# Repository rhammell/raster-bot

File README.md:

# Raster Bot

Raster Bot is a compact, two-wheeled differential-drive robot built around an
ESP32 and a capacitive touchscreen display. The project is fully open: it
includes the custom PCB, the 3D-printable mechanical design, the firmware
(packaged as an Arduino library), and the source graphics.

The firmware provides closed-loop motor control with quadrature encoders and
PID speed regulation, battery/charge monitoring, and a touchscreen UI — all
wrapped in a simple high-level API so sketches can drive the bot in a few lines.

## Build guide

A full step-by-step build tutorial — bill of materials, wiring, assembly, and
flashing — is published on Hackster.io:

**[Raster Bot build guide on Hackster.io](https://www.hackster.io/)** <!-- TODO: replace with the real tutorial URL -->

This README focuses on the contents of the repository and the firmware API;
see the Hackster guide if you want to build one from scratch.

## Repository structure

| Folder | Description |
| --- | --- |
| [`firmware/`](firmware/) | ESP32 firmware, packaged as the `Raster_Bot` Arduino library, plus example and tuning sketches. |
| [`hardware/`](hardware/) | KiCad project for the custom PCB (schematic, board layout, and footprint/symbol libraries). |
| [`mechanical/`](mechanical/) | FreeCAD model of the chassis and mechanical parts. |
| [`graphics/`](graphics/) | Logo artwork — SVG source and exported PNGs used for the board silkscreen and the boot splash screen. |

### `firmware/`

The firmware lives in `firmware/Raster_Bot/`, structured as an Arduino library:

| Path | Description |
| --- | --- |
| `src/Raster_Bot.h` / `.cpp` | Top-level `Raster_Bot` class that ties the subsystems together. |
| `src/definitions/` | Compile-time configuration: `pin_definitions.h` (wiring) and `robot_definitions.h` (tuning/behavior). |
| `src/display/` | `Raster_Display` — TFT, capacitive touch, and backlight control (plus the splash logo). |
| `src/battery/` | `Raster_Battery` — battery voltage and charger-status monitoring. |
| `src/drive/` | Differential drive stack: `Raster_Motor`, `Raster_Encoder`, `Raster_PID`, `Raster_Motor_Controller`, and `Raster_Drive`. |
| `examples/` | Standalone feature demos: `BatteryTest`, `GraphicsTest`, `TouchTest`. |
| `tuning/` | Calibration sketches, numbered in the order they should be run: `1_FeedforwardTuning`, `2_PIDTuning`, `3_WheelSyncTuning`, `4_DistanceTuning`. |
| `tests/` | Post-build verification sketches: `ForwardTest`, `DriftTest`. |
| `library.properties` | Arduino library metadata and dependencies. |

**Dependencies** (install via the Arduino Library Manager): Adafruit GFX
Library, Adafruit ILI9341, Adafruit FT6206 Library. Target architecture is
`esp32`.

### `hardware/`

KiCad design for the Raster Bot PCB. Open `hardware/Raster_Bot/Raster_Bot.kicad_pro`
in KiCad to view the schematic and board. Project-local footprint, symbol, and
3D-model libraries are under `hardware/Raster_Bot/libraries/`.

### `mechanical/`

FreeCAD source (`mechanical/src/Raster_Bot.FCStd`) for the robot's mechanical
design, parameterized for resizing.

### `graphics/`

- `src/raster_logo.svg` — master logo artwork.
- `export/raster_logo_silkscreen.png` — logo for the PCB silkscreen.
- `export/raster_logo_splash.png` — logo shown on the display at boot.

## Firmware API

Include the library and create a single `Raster_Bot` instance. It exposes three
subsystems as public members: `display`, `battery`, and `drive`.

```cpp
#include <Raster_Bot.h>

Raster_Bot bot;

void setup() {
    Serial.begin(115200);
    if (!bot.begin()) {
        Serial.println("Raster Bot init failed");
        while (1);
    }
    bot.drive.straight(10.0f);   // drive forward at 10 cm/s
}

void loop() {
    bot.drive.update();          // must be called frequently for PID control
}
```

### `Raster_Bot`

| Method | Description |
| --- | --- |
| `bool begin()` | Initializes the display, battery monitor, and drive subsystems. Returns `false` if any fail. |
| `display` | `Raster_Display` instance (see below). |
| `battery` | `Raster_Battery` instance (see below). |
| `drive` | `Raster_Drive` instance (see below). |

### `Raster_Display`

Extends Adafruit's `Adafruit_ILI9341`, so all standard Adafruit GFX drawing
calls are available in addition to:

| Method | Description |
| --- | --- |
| `bool begin()` | Initializes the TFT, touchscreen, and backlight. |
| `void showSplash()` | Plays the boot splash animation. |
| `void setBrightness(uint8_t brightness)` | Sets backlight brightness (0–255). |
| `bool touched()` | Returns `true` while the screen is being touched. |
| `TS_Point getTouchPoint()` | Returns the current touch point, mapped to the active screen rotation. |

### `Raster_Battery`

| Method | Description |
| --- | --- |
| `void begin()` | Initializes battery/charge-status monitoring. |
| `float voltage()` | Battery voltage in volts. |
| `bool charging()` | `true` while actively charging. |
| `bool chargerConnected()` | `true` when a charging source is plugged in. |

### `Raster_Drive`

Differential drive with per-wheel PID speed control. Call `update()` frequently
from `loop()` to run the control loop.

| Method | Description |
| --- | --- |
| `bool begin()` | Initializes the motor driver, both motor controllers, and encoders. |
| `void straight(float speed_cm_s)` | Drives both wheels at the given speed (negative = reverse). |
| `void stop()` | Stops both motors and goes idle. |
| `void update()` | Runs the drive control loop; call as often as possible. |
| `bool isMoving()` | `true` while a drive command is active. |
| `DriveTelemetry getTelemetry()` | Returns current motor telemetry. |
| `float getDistance()` | Returns cumulative straight-line distance, in cm, driven since power-on. |
| `void resetDistance()` | Resets the cumulative drive distance to zero. |

`DriveTelemetry` contains: `leftRPM`, `leftPWM`, `rightRPM`, `rightPWM`,
`leftCount`, and `rightCount` (wheel-output RPM and raw encoder counts).

## License

<!-- TODO: add a license (e.g. MIT for firmware, CERN-OHL or CC-BY-SA for hardware). -->

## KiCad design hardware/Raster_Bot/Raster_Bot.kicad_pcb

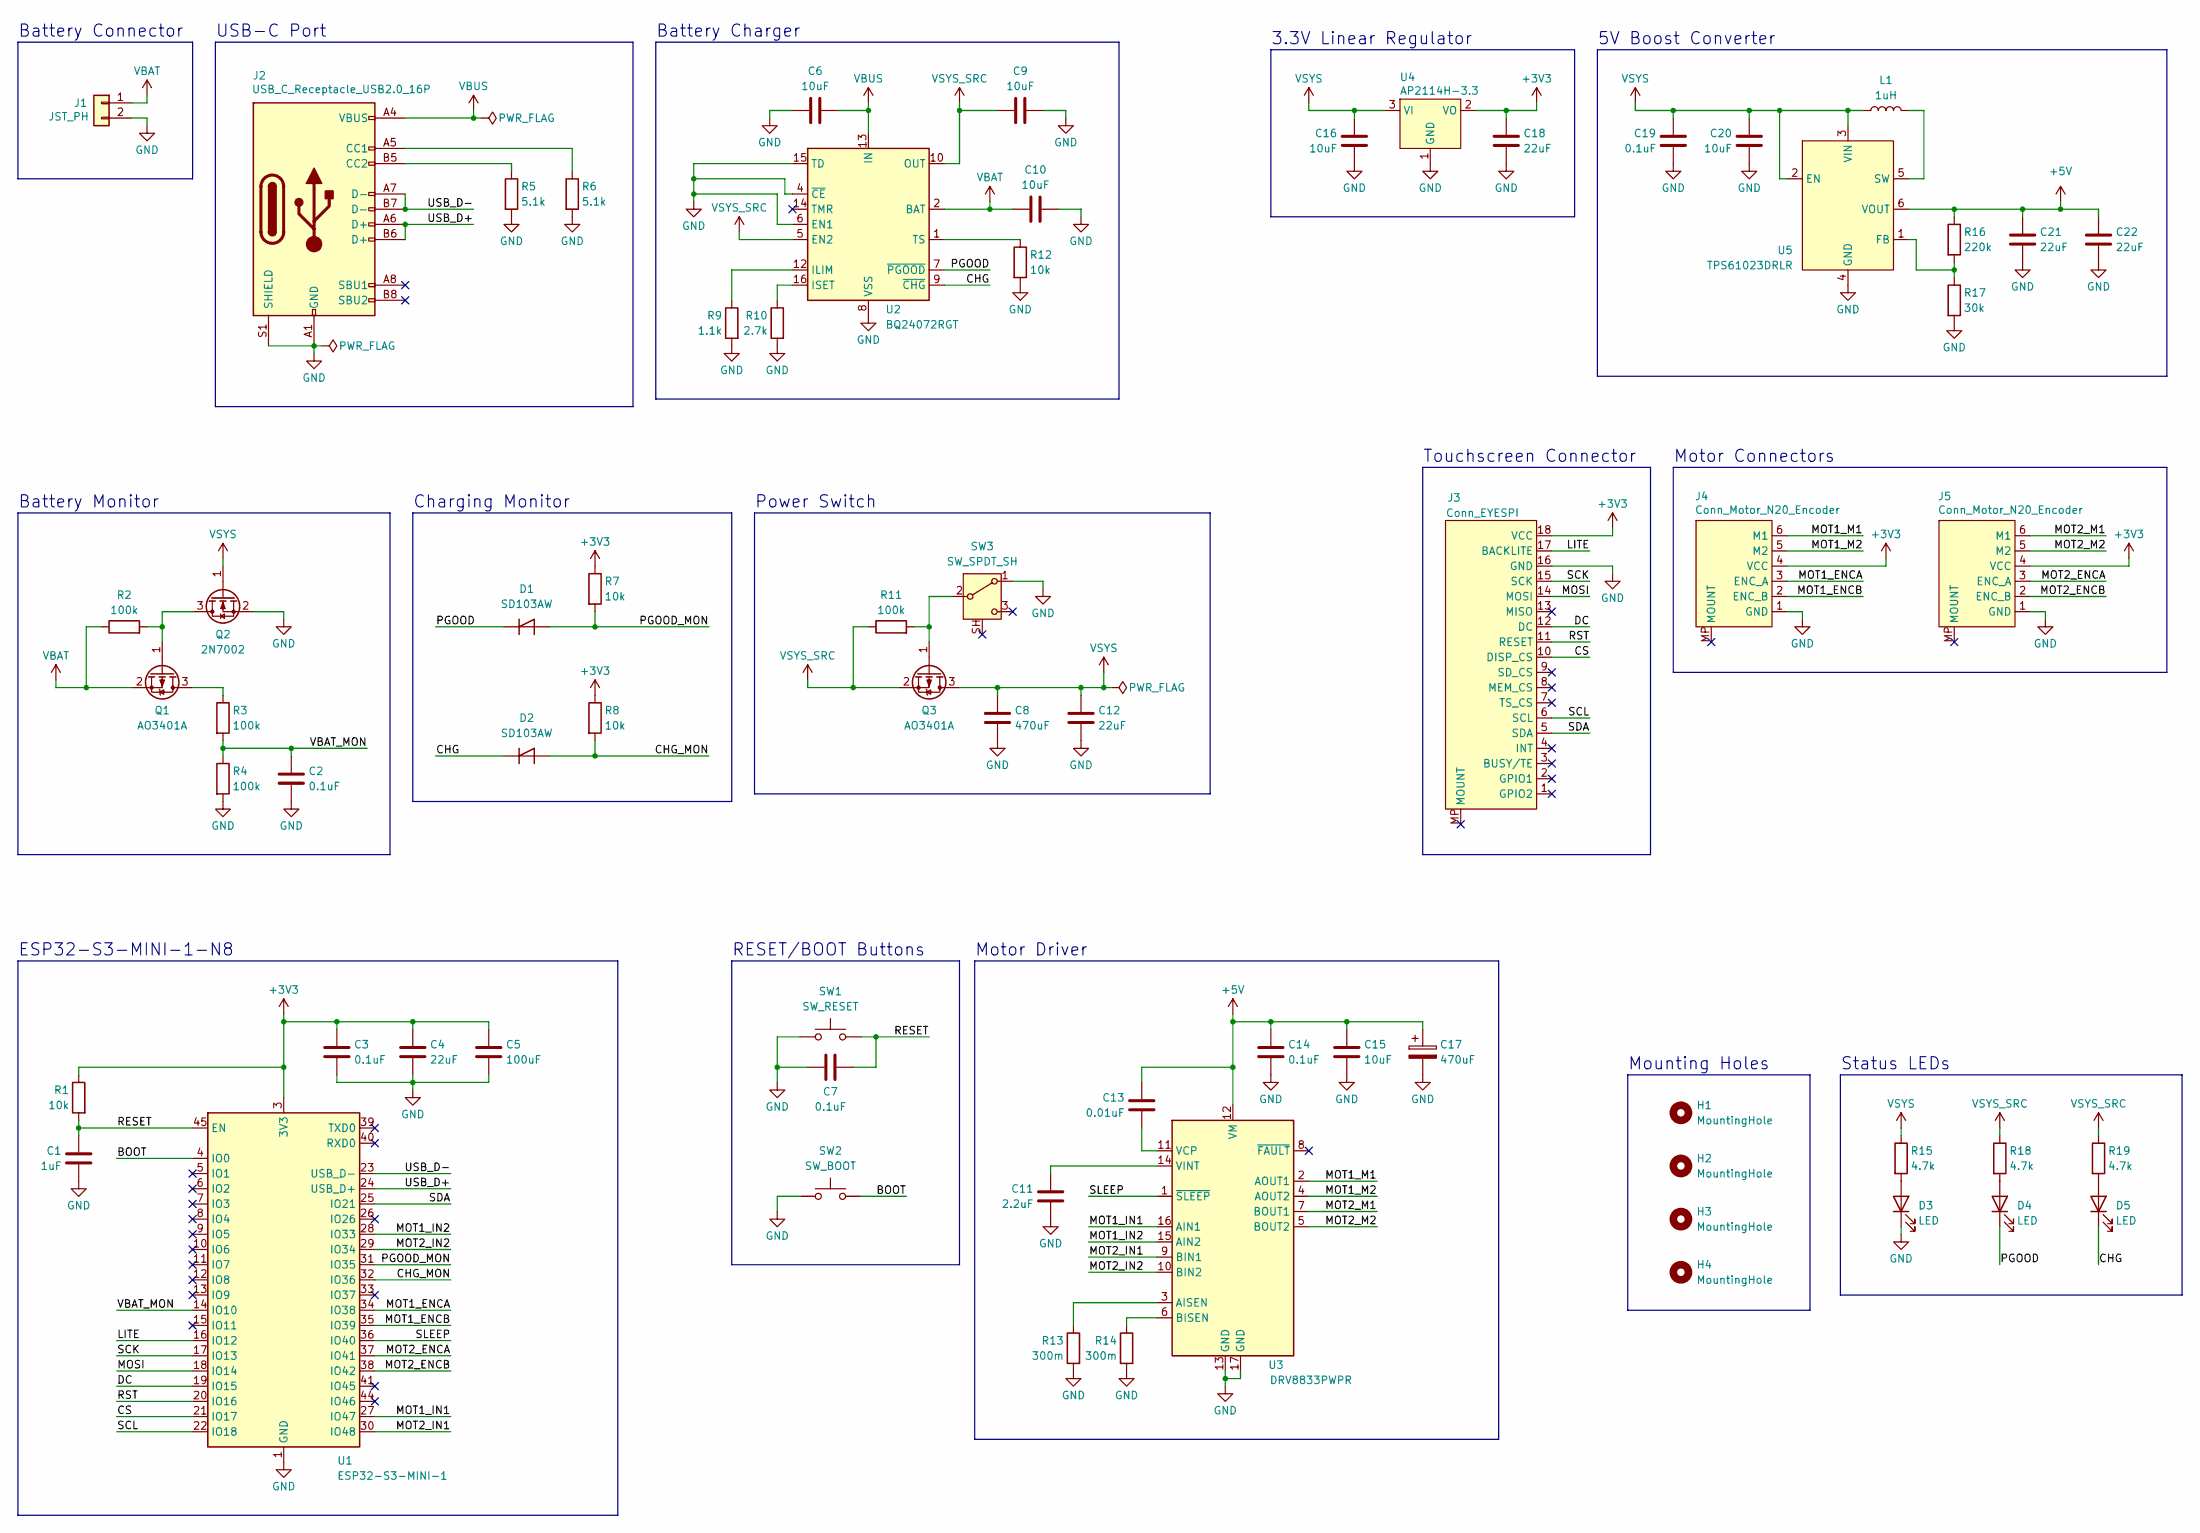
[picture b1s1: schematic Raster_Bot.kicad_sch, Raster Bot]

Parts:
C1: 1uF; C_0603_1608Metric; LCSC C15849
C2, C3, C7, C14, C19: 0.1uF; C_0603_1608Metric; LCSC C14663
C4, C12, C18, C21, C22: 22uF; C_0805_2012Metric; LCSC C45783
C5: 100uF; C_1206_3216Metric; LCSC C15008
C6, C9, C10, C15, C16, C20: 10uF; C_0805_2012Metric; LCSC C15850
C8, C17: 470uF; CP_Elec_6.3x7.7; LCSC C344072
C11: 2.2uF; C_0603_1608Metric; LCSC C23630
C13: 0.01uF; C_0603_1608Metric; LCSC C57112
D1, D2: SD103AW; D_SOD-123; LCSC C7502706
D3: LED; LED_0805_2012Metric; LCSC C2297
D4, D5: LED; LED_0805_2012Metric; LCSC C2296
H1, H2, H3, H4: MountingHole; MountingHole_2.7mm_M2.5
J1: JST_PH; JST_PH_B2B-PH-K_1x02_P2.00mm_Vertical; LCSC C131337
J2: USB_C_Receptacle_USB2.0_16P; USB_C_Receptacle_G-Switch_GT-USB-7010ASV; LCSC C2988369
J3: Conn_EYESPI; XUNPU_FPC-05F-18PH20_1x18-1MP_P0.5mm_Horizontal; LCSC C2856802
J4, J5: Conn_Motor_N20_Encoder; JST_SH_BM06B-SRSS-TB_1x06-1MP_P1.00mm_Vertical; LCSC C495540
L1: 1uH; L_Coilcraft_XxL4030; LCSC C5441341
Q1, Q3: AO3401A; SOT-23; LCSC C15127
Q2: 2N7002; SOT-23; LCSC C8545
R1, R7, R8, R12: 10k; R_0603_1608Metric; LCSC C25804
R2, R3, R4, R11: 100k; R_0603_1608Metric; LCSC C25803
R5, R6: 5.1k; R_0603_1608Metric; LCSC C23186
R9: 1.1k; R_0603_1608Metric; LCSC C22764
R10: 2.7k; R_0603_1608Metric; LCSC C13167
R13, R14: 300m; R_1206_3216Metric; LCSC C22464904
R15, R18, R19: 4.7k; R_0603_1608Metric; LCSC C23162
R16: 220k; R_0603_1608Metric; LCSC C22961
R17: 30k; R_0603_1608Metric; LCSC C22984
SW1: SW_RESET; SW_SPST_TS-1088-xR020; LCSC C720477
SW2: SW_BOOT; SW_SPST_TS-1088-xR020; LCSC C720477
SW3: SW_SPDT_SH; SW_SPDT_Shouhan_MSK12C02; LCSC C431541
U1: ESP32-S3-MINI-1; LCSC C2913206
U2: BQ24072RGT; VQFN-16-1EP_3x3mm_P0.5mm_EP1.6x1.6mm_ThermalVias; LCSC C140288
U3: DRV8833PWPR; HTSSOP-16-1EP_4.4x5mm_P0.65mm_EP3.4x5mm_Mask2.66x2.46mm_The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; LCSC C50506
U4: AP2114H-3.3; SOT-223-3_TabPin2; LCSC C150716
U5: TPS61023DRLR; SOT-563; LCSC C919459

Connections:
+3V3: C3.1, C4.1, C5.1, C18.1, J3.18 (VCC), J4.4 (VCC), J5.4 (VCC), R1.1, R7.1, R8.1, U1.3 (3V3), U4.2 (VO)
+5V: C13.1, C14.1, C15.1, C17.1, C21.1, C22.1, R16.1, U3.12 (VM), U5.6 (VOUT)
/BOOT: SW2.2, U1.4 (IO0)
/CHG: D2.1 (K), D5.1 (K), U2.9 (~CHG)
/CHG_MON: D2.2 (A), R8.2, U1.32 (IO36)
/CS: J3.10 (DISP_CS), U1.21 (IO17)
/DC: J3.12 (DC), U1.19 (IO15)
/LITE: J3.17 (BACKLITE), U1.16 (IO12)
/MOSI: J3.14 (MOSI), U1.18 (IO14)
/MOT1_ENCA: J4.3 (ENC_A), U1.34 (IO38)
/MOT1_ENCB: J4.2 (ENC_B), U1.35 (IO39)
/MOT1_IN1: U1.27 (IO47), U3.16 (AIN1)
/MOT1_IN2: U1.28 (IO33), U3.15 (AIN2)
/MOT1_M1: J4.6 (M1), U3.2 (AOUT1)
/MOT1_M2: J4.5 (M2), U3.4 (AOUT2)
/MOT2_ENCA: J5.3 (ENC_A), U1.37 (IO41)
/MOT2_ENCB: J5.2 (ENC_B), U1.38 (IO42)
/MOT2_IN1: U1.30 (IO48), U3.9 (BIN1)
/MOT2_IN2: U1.29 (IO34), U3.10 (BIN2)
/MOT2_M1: J5.6 (M1), U3.7 (BOUT1)
/MOT2_M2: J5.5 (M2), U3.5 (BOUT2)
/PGOOD: D1.1 (K), D4.1 (K), U2.7 (~PGOOD)
/PGOOD_MON: D1.2 (A), R7.2, U1.31 (IO35)
/RESET: C1.1, C7.1, R1.2, SW1.2, U1.45 (EN)
/RST: J3.11 (RESET), U1.20 (IO16)
/SCK: J3.15 (SCK), U1.17 (IO13)
/SCL: J3.6 (SCL), U1.22 (IO18)
/SDA: J3.5 (SDA), U1.25 (IO21)
/SLEEP: U1.36 (IO40), U3.1 (~SLEEP)
/USB_D+: J2.A6 (D+), J2.B6 (D+), U1.24 (USB_D+)
/USB_D-: J2.A7 (D-), J2.B7 (D-), U1.23 (USB_D-)
/VBAT_MON: C2.1, R3.2, R4.1, U1.14 (IO10)
GND: C1.2, C2.2, C3.2, C4.2, C5.2, C6.1, C7.2, C8.2, C9.2, C10.2, C11.2, C12.2, C14.2, C15.2, C16.2, C17.2, C18.2, C19.2, C20.2, C21.2, C22.2, D3.1 (K), J1.2, J2.A1 (GND), J2.A12 (GND), J2.B1 (GND), J2.B12 (GND), J2.S1 (SHIELD), J3.16 (GND), J4.1 (GND), J5.1 (GND), Q2.2 (S), R4.2, R5.2, R6.2, R9.2, R10.2, R12.2, R13.2, R14.2, R17.2, SW1.1, SW2.1, SW3.1 (A), U1.1 (GND), U1.2 (GND), U1.42 (GND), U1.43 (GND), U1.46 (GND), U1.47 (GND), U1.48 (GND), U1.49 (GND), U1.50 (GND), U1.51 (GND), U1.52 (GND), U1.53 (GND), U1.54 (GND), U1.55 (GND), U1.56 (GND), U1.57 (GND), U1.58 (GND), U1.59 (GND), U1.60 (GND), U1.61 (GND), U1.62 (GND), U1.63 (GND), U1.64 (GND), U1.65 (GND), U2.4 (~CE), U2.6 (EN1), U2.8 (VSS), U2.15 (TD), U2.17 (VSS), U3.13 (GND), U3.17 (GND), U4.1 (GND), U5.4 (GND)
unnamed: D3.2 (A), R15.2
unnamed: D4.2 (A), R18.2
unnamed: D5.2 (A), R19.2
unnamed: J2.A5 (CC1), R6.1
unnamed: J2.B5 (CC2), R5.1
unnamed: Q1.3 (D), R3.1
unnamed: Q1.1 (G), Q2.3 (D), R2.2
unnamed: Q3.1 (G), R11.2, SW3.2 (B)
unnamed: R9.1, U2.12 (ILIM)
unnamed: R10.1, U2.16 (ISET)
unnamed: R12.1, U2.1 (TS)
unnamed: R13.1, U3.3 (AISEN)
unnamed: R14.1, U3.6 (BISEN)
unnamed: C13.2, U3.11 (VCP)
unnamed: C11.1, U3.14 (VINT)
unnamed: R16.2, R17.1, U5.1 (FB)
unnamed: L1.2, U5.5 (SW)
VBAT: C10.1, J1.1, Q1.2 (S), R2.1, U2.2 (BAT), U2.3 (BAT)
VBUS: C6.2, J2.A4 (VBUS), J2.A9 (VBUS), J2.B4 (VBUS), J2.B9 (VBUS), U2.13 (IN)
VSYS: C8.1, C12.1, C16.1, C19.1, C20.1, L1.1, Q2.1 (G), Q3.3 (D), R15.1, U4.3 (VI), U5.2 (EN), U5.3 (VIN)
VSYS_SRC: C9.1, Q3.2 (S), R11.1, R18.1, R19.1, U2.5 (EN2), U2.10 (OUT), U2.11 (OUT)

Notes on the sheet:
Motor Connectors
ESP32-S3-MINI-1-N8
RESET/BOOT Buttons
Battery Charger
Battery Monitor
Touchscreen Connector
Charging Monitor
5V Boost Converter
Status LEDs
3.3V Linear Regulator
Mounting Holes
USB-C Port
Battery Connector
Power Switch
Motor Driver

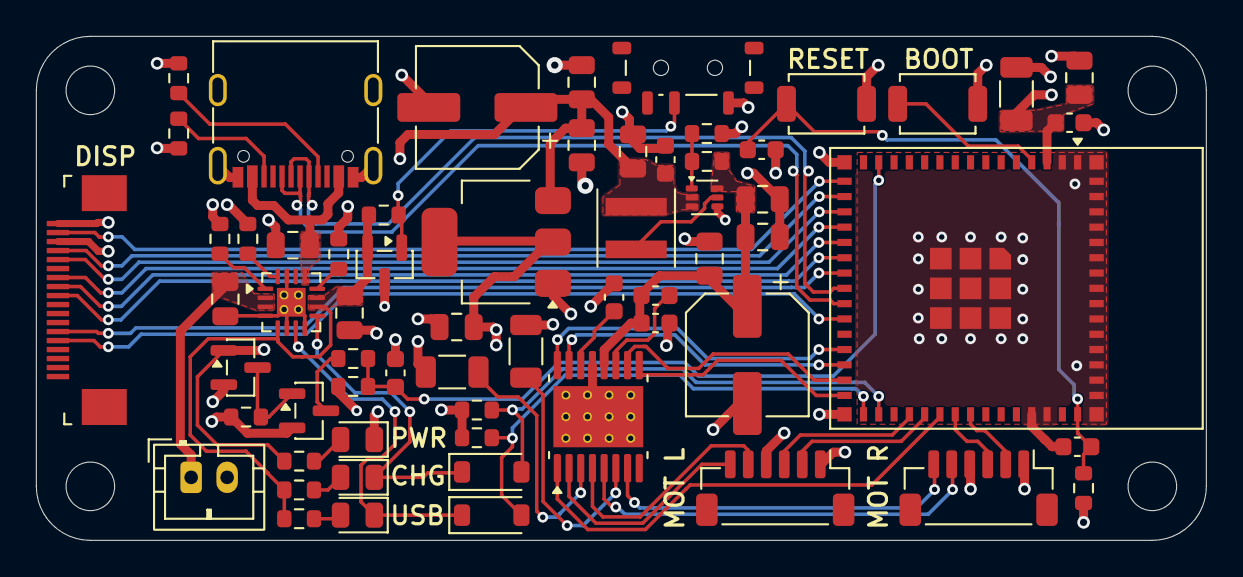
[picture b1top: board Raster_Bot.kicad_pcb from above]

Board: 4 copper layers, 65.0 x 28.0 mm, 67 parts (0 on the bottom side), 54 nets.

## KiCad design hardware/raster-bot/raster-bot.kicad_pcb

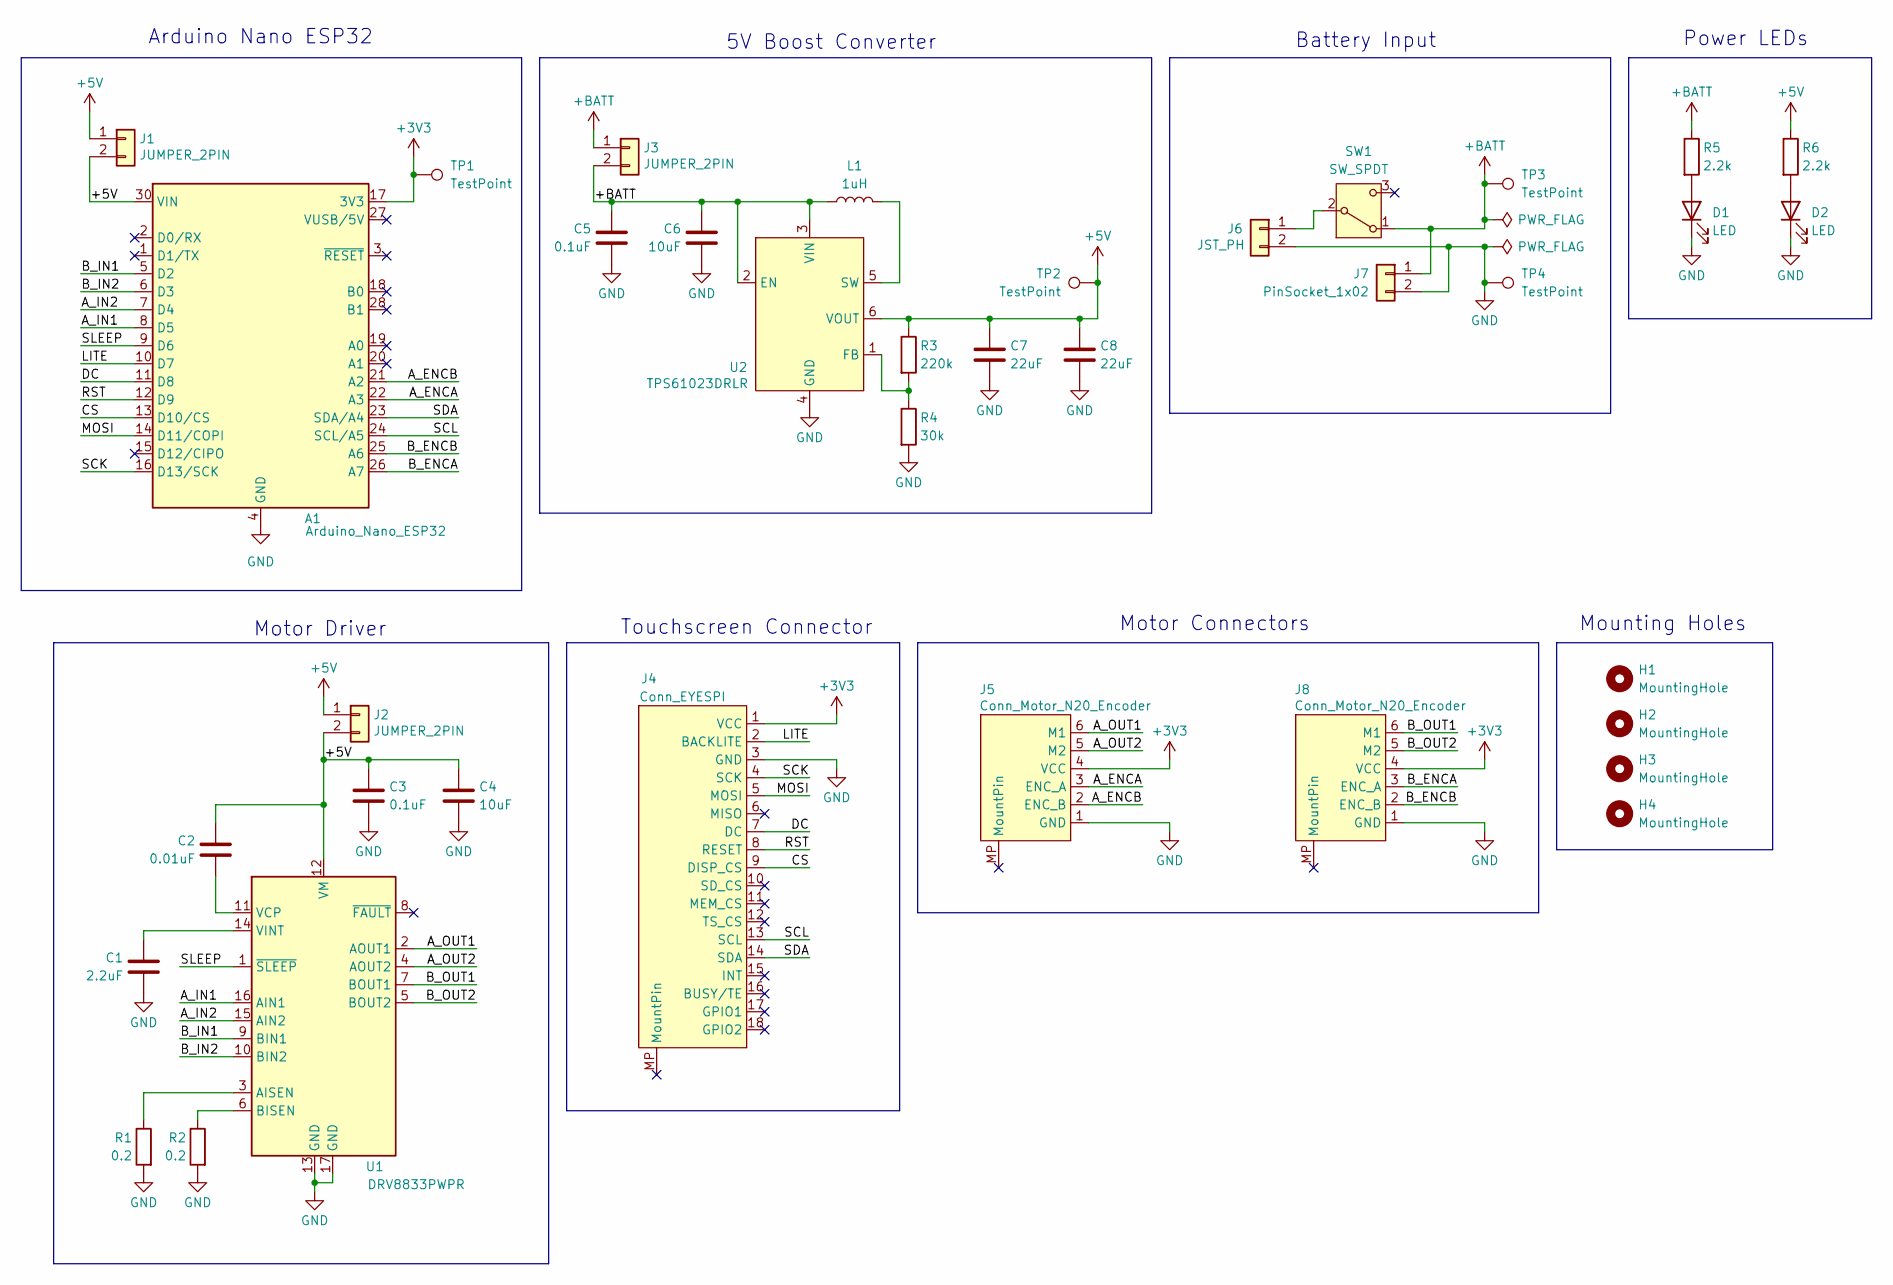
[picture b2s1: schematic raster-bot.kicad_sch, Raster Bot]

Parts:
A1: Arduino_Nano_ESP32; Arduino_Nano
C1: 2.2uF; C_0805_2012Metric; Voltage 6.3; LCSC C377773
C2: 0.01uF; C_0805_2012Metric; Voltage 16; LCSC C1710
C3, C5: 0.1uF; C_0805_2012Metric; LCSC C28233
C4, C6: 10uF; C_0805_2012Metric; LCSC C15850
C7, C8: 22uF; C_0805_2012Metric; LCSC C45783
D1, D2: LED; LED_0603_1608Metric; LCSC C2286
H1, H2, H3, H4: MountingHole; MountingHole_3.2mm_M3
J1, J2, J3: JUMPER_2PIN; PinHeader_1x02_P2.54mm_Vertical; LCSC C124375
J4: Conn_EYESPI; LCSC C2856802
J5, J8: Conn_Motor_N20_Encoder; LCSC C495540
J6: JST_PH; JST_PH_B2B-PH-K_1x02_P2.00mm_Vertical; LCSC C131337
J7: PinSocket_1x02; PinSocket_1x02_P2.54mm_Vertical
L1: 1uH; L_Coilcraft_XxL4030; LCSC C5441341
R1, R2: 0.2; R_1206_3216Metric; LCSC C7467885
R3: 220k; R_0603_1608Metric; LCSC C22961
R4: 30k; R_0603_1608Metric; LCSC C22984
R5, R6: 2.2k; R_0603_1608Metric; LCSC C4190
SW1: SW_SPDT; SW_SPDT_Shouhan_MSK12C02; LCSC C431541
TP1, TP2, TP3, TP4: TestPoint; TestPoint_Pad_1.5x1.5mm
U1: DRV8833PWPR; HTSSOP-16-1EP_4.4x5mm_P0.65mm_EP3.4x5mm_Mask2.66x2.46mm_The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; LCSC C50506
U2: TPS61023DRLR; SOT-563; LCSC C919459

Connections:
+3V3: A1.17 (3V3), J4.1 (VCC), J5.4 (VCC), J8.4 (VCC), TP1.1
+5V: A1.30 (VIN), C2.1, C3.1, C4.1, C7.1, C8.1, J1.1, J1.2, J2.1, J2.2, R3.1, R6.1, TP2.1, U1.12 (VM), U2.6 (VOUT)
+BATT: C5.1, C6.1, J3.1, J3.2, J7.1, L1.1, R5.1, SW1.1 (A), TP3.1, U2.2 (EN), U2.3 (VIN)
/A_ENCA: A1.22 (A3), J5.3 (ENC_A)
/A_ENCB: A1.21 (A2), J5.2 (ENC_B)
/A_IN1: A1.8 (D5), U1.16 (AIN1)
/A_IN2: A1.7 (D4), U1.15 (AIN2)
/A_OUT1: J5.6 (M1), U1.2 (AOUT1)
/A_OUT2: J5.5 (M2), U1.4 (AOUT2)
/B_ENCA: A1.26 (A7), J8.3 (ENC_A)
/B_ENCB: A1.25 (A6), J8.2 (ENC_B)
/B_IN1: A1.5 (D2), U1.9 (BIN1)
/B_IN2: A1.6 (D3), U1.10 (BIN2)
/B_OUT1: J8.6 (M1), U1.7 (BOUT1)
/B_OUT2: J8.5 (M2), U1.5 (BOUT2)
/CS: A1.13 (D10/CS), J4.9 (DISP_CS)
/DC: A1.11 (D8), J4.7 (DC)
/LITE: A1.10 (D7), J4.2 (BACKLITE)
/MOSI: A1.14 (D11/COPI), J4.5 (MOSI)
/RST: A1.12 (D9), J4.8 (RESET)
/SCK: A1.16 (D13/SCK), J4.4 (SCK)
/SCL: A1.24 (SCL/A5), J4.13 (SCL)
/SDA: A1.23 (SDA/A4), J4.14 (SDA)
/SLEEP: A1.9 (D6), U1.1 (~SLEEP)
GND: A1.4 (GND), A1.29 (GND), C1.2, C3.2, C4.2, C5.2, C6.2, C7.2, C8.2, D1.1 (K), D2.1 (K), J4.3 (GND), J5.1 (GND), J6.2, J7.2, J8.1 (GND), R1.2, R2.2, R4.2, TP4.1, U1.13 (GND), U1.17 (GND), U2.4 (GND)
unnamed: D1.2 (A), R5.2
unnamed: D2.2 (A), R6.2
unnamed: J6.1, SW1.2 (B)
unnamed: R1.1, U1.3 (AISEN)
unnamed: R2.1, U1.6 (BISEN)
unnamed: C2.2, U1.11 (VCP)
unnamed: C1.1, U1.14 (VINT)
unnamed: R3.2, R4.1, U2.1 (FB)
unnamed: L1.2, U2.5 (SW)

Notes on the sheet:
Battery Input
Power LEDs
Motor Connectors
Mounting Holes
Touchscreen Connector
Motor Driver
5V Boost Converter
Arduino Nano ESP32

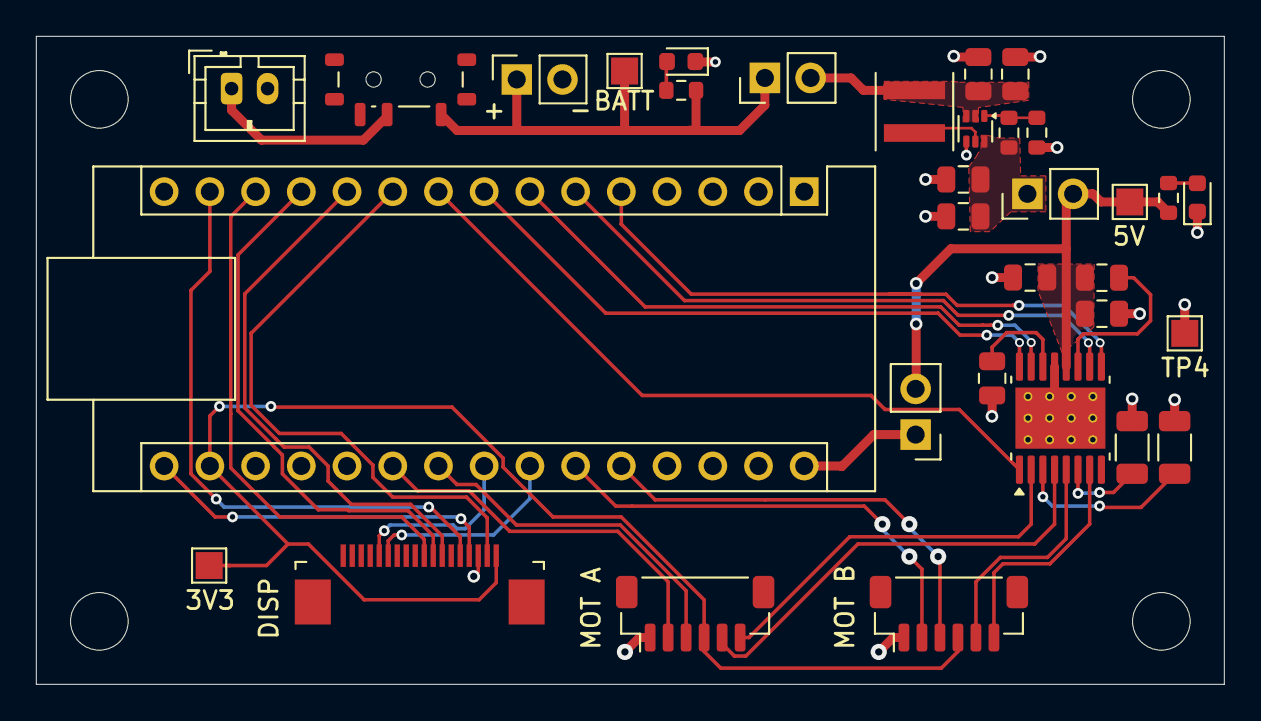
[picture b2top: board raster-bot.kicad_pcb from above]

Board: 2 copper layers, 66.0 x 36.0 mm, 37 parts (0 on the bottom side), 34 nets.

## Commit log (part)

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2026-01-16 Initial commit of v0.1 of hardware PCB design
2026-01-18 PCB v0.2 update - added motor JST connectors; refactored custom footprints
2026-01-28 Refactor filenames to Raster_Bot
2026-02-11 Add initial implementation of Raster_Bot library with configuration, display, and touch functionality; include example sketches for graphics and touch tests.
2026-02-11 Update hardware design for Raster Bot: modified schematic to include USB-C receptacle, adjusted component properties, and refined sorting options in the project configuration.
2026-02-11 Remove obsolete raster-bot.kicad_pro file, cleaning up the project structure.
2026-03-09 [hardware] v0.3 - design upgrade featuring esp32-s3, battery charger, 3.3V LDO, 5V boost coverter
2026-03-09 [hardware] Add version silkscreen;
2026-03-10 [firmware] Battery voltage and charge monitoring added; Including new example
2026-03-27 [hardware] v0.4 - 4 layer PCB design with ESP32-S3-MINI
2026-03-31 [firmware] Refactor of display and battery classes; library properties updated
2026-04-01 [firmware] Update display and battery configurations; refactor SPI and I2C initialization
2026-04-14 [firmware] Refactor BatteryTest example to improve text display; replace centered text with fixed position rows
2026-04-17 [firmware] Update config for v0.4 hardware; Initial implementation of drive API, including motor controller, motor, encoder, and PID classes
2026-04-18 [firmware] Refactor drive update logic to use elapsed time and update motor controller to accept time delta
2026-04-28 [hardware] v0.5 - Add motor driver bulk capacitor; Remove test pads and jumpers
2026-04-29 [hardware] Chage ISEN resistor values, part, and placement
2026-04-29 [firmware] Add splash screen display on startup
    Add showSplash() method to Raster_Display that shows centered
    "Raster Bot" text for a configurable duration. Add splash call
    to GraphicsTest, TouchTest, and BatteryTest examples. Also add
    serial debug printouts to display initialization for easier
    troubleshooting.
    Made-with: Cursor
2026-05-01 [firmware] Add bitmap logo splash screen with fade in/out
    Replace text-based splash with monochrome bitmap logo drawn from
    splash_logo.h. Add backlight fade in/out using analogWrite PWM
    control. Simplify showSplash() to take no parameters with a
    hardcoded 3-second duration.
    Made-with: Cursor
2026-05-01 [firmware] Adjust splash screen timing and add black pauses
    Slow fade in/out to ~1s each, add 250ms black pause before fade-in
    and 500ms black hold after fade-out for smoother transitions.
    Made-with: Cursor
2026-05-01 [firmware] Add comments and adjust splash timing
    Add descriptive comments to showSplash() steps. Adjust fade
    delay to 10ms and hold duration to 2000ms.
    Made-with: Cursor
2026-05-16 [hardware] v0.6 - Add silkscreen logo; Reposition footprints; Remove custom USB footprint
2026-05-16 [graphics] Update raster logo SVG settings for improved export
2026-05-17 [mechanical] Init commit of FreeCAD design file
2026-05-18 Update gitignore
2026-05-18 [mechanical] Move FreeCAD design file to src directory and delete old location
2026-05-20 [mechanical] Rough enclosure lid and base
2026-05-21 [mechanical] Update Raster_Bot.FCStd design file
2026-05-31 [mechanical] Update Raster_Bot.FCStd design file with new changes
2026-05-31 [mechanical] Update Raster_Bot.FCStd design file with additional modifications
2026-06-01 [mechanical] Update Raster_Bot.FCStd design file with latest modifications
2026-06-02 [mechanical] Update Raster_Bot.FCStd design file with recent changes
2026-06-03 [mechanical] Refresh Raster_Bot.FCStd design file with updated features
2026-06-04 [mechanical] Refresh Raster_Bot.FCStd design file with new updates
2026-06-06 [mechanical] Refresh Raster_Bot.FCStd design file with latest updates
2026-06-09 [hardware] v0.7 - Added bulk capacitance; PCB layout update
2026-06-11 [hardware] Update PCB UUIDs for components in Raster_Bot.kicad_pcb
2026-06-14 [mechanical] Add test stand model
2026-06-14 [mechanical] Test stand constraint correction to prevent flipping
2026-06-14 [firmware] Refactor motor and encoder status retrieval into single getStatus() method; Update all example/test sketches to utilize this
2026-06-16 [firmware] Update PID tuning sketch to clamp drive speed and add PWM display
2026-06-16 [firmware] Restore proportional correction for wheel speed to maintain straight driving; Update motor controller to use private member variables.
2026-06-19 [mechanical] Modify wheel with robust parameters for error free resizing
2026-06-20 [mechanical] Modify test stand constraints for error free resizing
2026-06-20 [mechanical] Add tire with robust parameters for resizing
2026-06-20 [mechanical] Update Raster_Bot design to improve resize robustness
2026-06-20 [firmware] Remove legacy pin configurations
2026-06-21 [firmware] Update PID tuning instructions to include MAX_ACCEL_RPM_S for ramping control
2026-06-21 [firmware] Adjust motor pin definitions for MOTOR_150 configuration
2026-06-21 [firmware] Implement ramped RPM control for smoother motor response
2026-06-21 [firmware] Remove BatteryLife and MotorStress test files
2026-06-24 [mechanical] STL exports of each component of bot housing
2026-06-25 [mechanical] Update Raster_Bot PCB and project file
